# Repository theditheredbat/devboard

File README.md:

# DevBoard
I decided to follow along with HackClub's Devboard tutorial,  
made by Kai Pereira, to get more comfortable with designing PCBs.  
Here's what I ended up with:  

## PCB
Made in KiCAD  
Schematic:  

PCB:  

## BOM
1x [RP2040](https://jlcpcb.com/partdetail/RaspberryPi-RP2040/C2040) $0.92  
1x [PCB](https://cart.jlcpcb.com/quote?spm=Jlcpcb.Homepage.1006) from JLCPCB $2.10  
2x [33pF Capacitors](https://jlcpcb.com/partdetail/1914-0402CG330J500NT/C1562) $0.01  
11x [0.1uF Capacitors](https://jlcpcb.com/partdetail/1877-CL05B104KO5NNNC/C1525) $0.01  
2x [1uF Capacitors](https://jlcpcb.com/partdetail/15107-CL05A105KP5NNNC/C14445) $0.01  
2x [10uF Capacitors](https://jlcpcb.com/partdetail/2043-CL10A106MQ8NNNC/C1691) $0.01  
2x [27 Resistors](https://jlcpcb.com/partdetail/2358-RCMT08W270JT/C2006) $0.01  
2x [1K Resistors](https://jlcpcb.com/partdetail/12256-0402WGF1001TCE/C11702) $0.01  
2x [5.1K Resistors](https://jlcpcb.com/partdetail/26684-0402WGJ0512TCE/C25941) $0.01  
1x [10K Resistor](https://jlcpcb.com/partdetail/26274-0402WGJ0103TCE/C25531) $0.01  
1x [PinHeader1x03P2.54mm_Vertical](https://jlcpcb.com/partdetail/HanElectricity-2541WR03P/C5383096) $0.01  
2x [PinHeader1x20P2.54mm_Vertical](https://jlcpcb.com/partdetail/244951-2_54_1_20P/C247921) $0.23  
1x [4Pin 2x2.5mm Quartz Clock](https://jlcpcb.com/partdetail/YXC_CrystalOscillators-X322512MSB4SI/C9002) $0.06  
1x [USB-C Receptacle](https://jlcpcb.com/partdetail/Korean_HropartsElec-TYPE_C_31_M12/C165948) $0.17  
1x [TS-1088-AR02016 Push Button](https://jlcpcb.com/partdetail/XUNPU-TS_1088AR02016/C720477) $0.04  
1x [MCP1700x-330xxTT Fixed Voltage Regulator](https://jlcpcb.com/partdetail/JLCPCBAssembly-MCP1700/C9900006637) $0.39  
1x [W25Q16JVZPIQ TR Flash Mem Chip](https://jlcpcb.com/partdetail/WinbondElec-W25Q16JVZPIQ/C377853) $0.35  
Estimated Shipping: $2.40
Estimated Total: $6.92

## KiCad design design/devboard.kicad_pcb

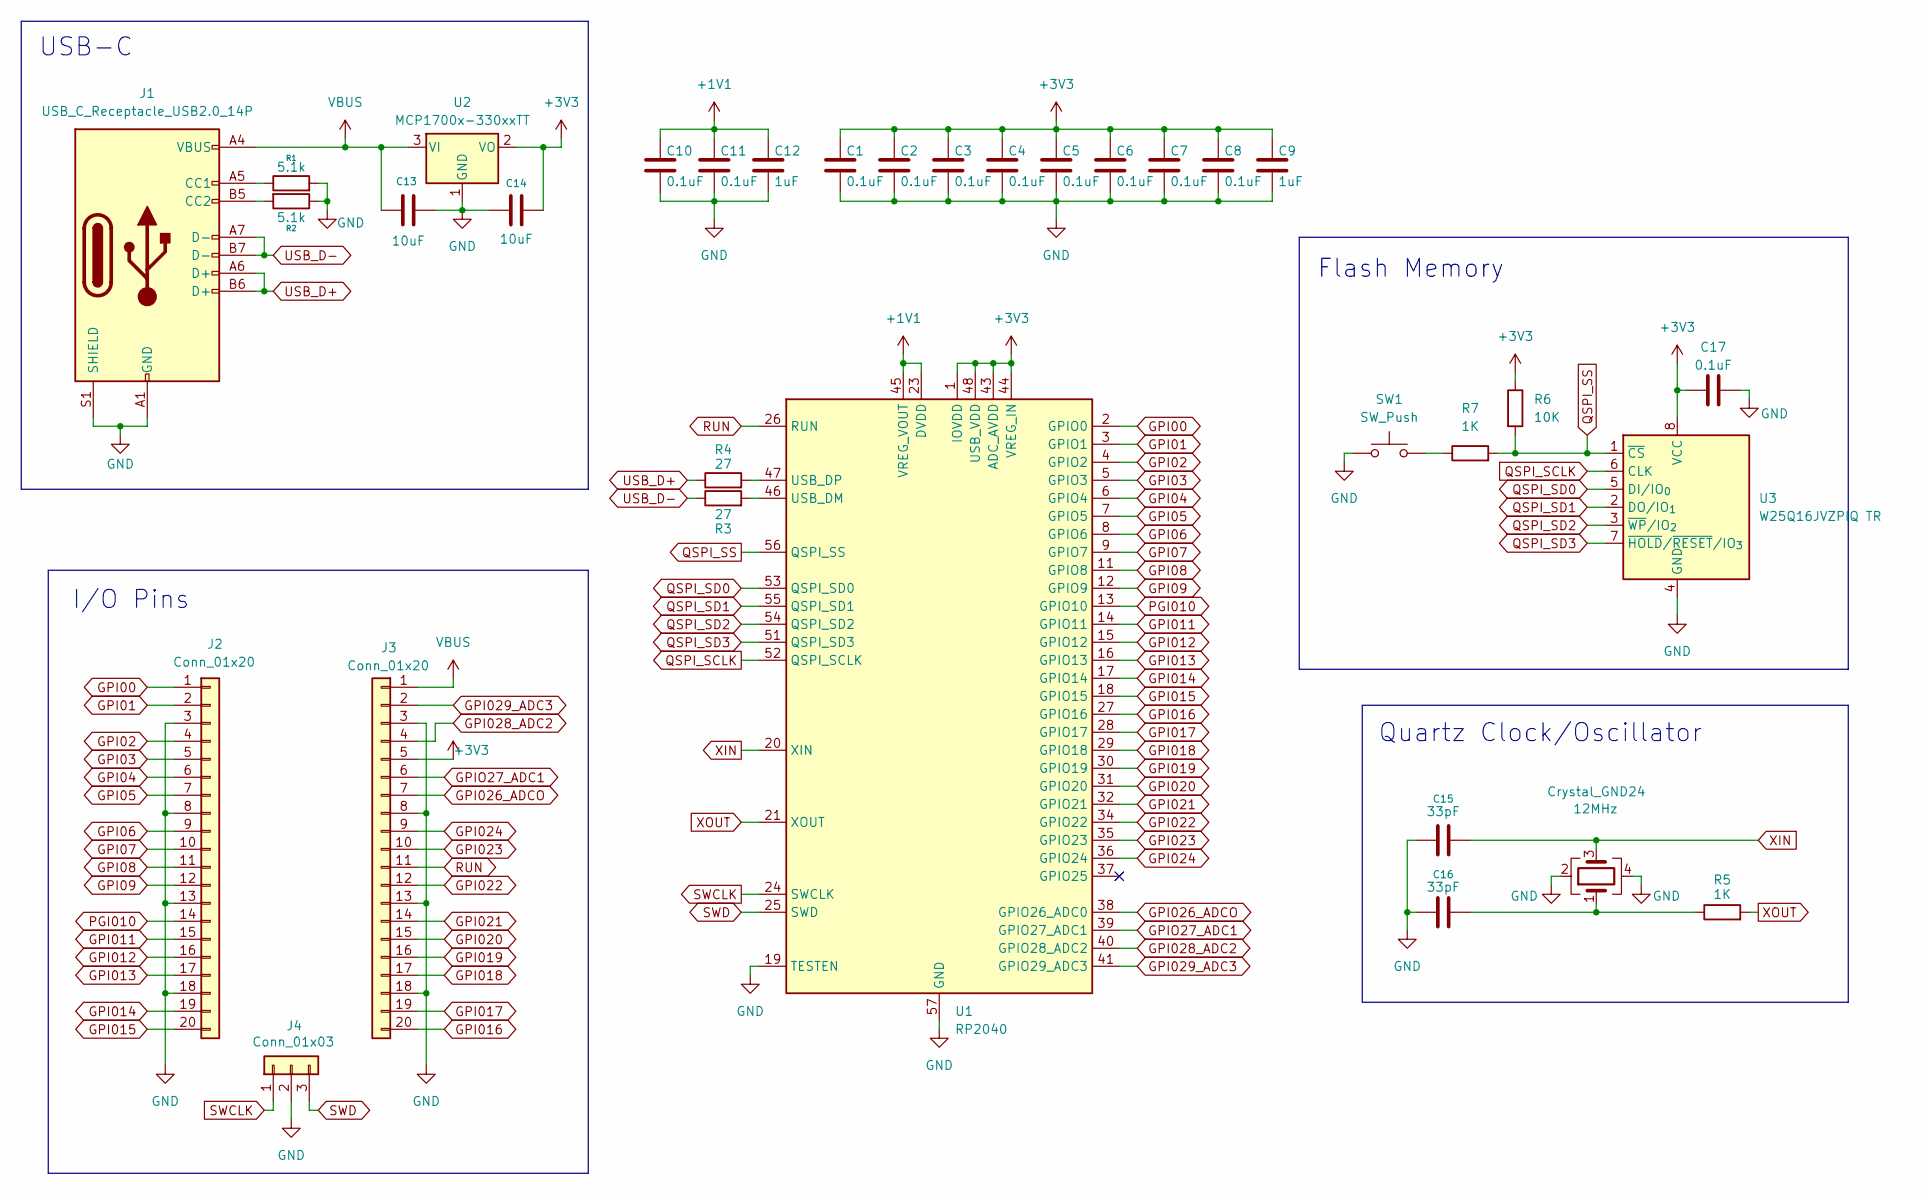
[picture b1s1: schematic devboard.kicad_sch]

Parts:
C1, C2, C3, C4, C5, C6, C7, C8, C10, C11, C17: 0.1uF; C_0402_1005Metric
C9, C12: 1uF; C_0402_1005Metric
C13, C14: 10uF; C_0603_1608Metric
C15, C16: 33pF; C_0402_1005Metric
Crystal_GND24: 12MHz; Crystal_SMD_3225-4Pin_3.2x2.5mm
J1: USB_C_Receptacle_USB2.0_14P; USB_C_Receptacle_HRO_TYPE-C-31-M-12
J2, J3: Conn_01x20; PinHeader_1x20_P2.54mm_Vertical
J4: Conn_01x03; PinHeader_1x03_P2.54mm_Vertical
R1, R2: 5.1k; R_0402_1005Metric
R3, R4: 27; R_0402_1005Metric
R5, R7: 1K; R_0402_1005Metric
R6: 10K; R_0402_1005Metric
SW1: SW_Push; SW_Push_SPST_NO_Alps_SKRK
U1: RP2040; QFN-56-1EP_7x7mm_P0.4mm_EP3.2x3.2mm
U2: MCP1700x-330xxTT; SOT-23
U3: W25Q16JVZPIQ TR; Winbond_USON-8-1EP_3x2mm_P0.5mm_EP0.2x1.6mm

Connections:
+1V1: C10.1, C11.1, C12.1, U1.23 (DVDD), U1.45 (VREG_VOUT), U1.50 (DVDD)
+3V3: C1.1, C2.1, C3.1, C4.1, C5.1, C6.1, C7.1, C8.1, C9.1, C14.2, C17.1, J3.5, R6.1, U1.1 (IOVDD), U1.10 (IOVDD), U1.22 (IOVDD), U1.33 (IOVDD), U1.42 (IOVDD), U1.43 (ADC_AVDD), U1.44 (VREG_IN), U1.48 (USB_VDD), U1.49 (IOVDD), U2.2 (VO), U3.8 (VCC)
GND: C1.2, C2.2, C3.2, C4.2, C5.2, C6.2, C7.2, C8.2, C9.2, C10.2, C11.2, C12.2, C13.2, C14.1, C15.1, C16.1, C17.2, Crystal_GND24.2, Crystal_GND24.4, J1.A1 (GND), J1.A12 (GND), J1.B1 (GND), J1.B12 (GND), J1.S1 (SHIELD), J2.3, J2.8, J2.13, J2.18, J3.3, J3.8, J3.13, J3.18, J4.2, R1.2, R2.1, SW1.1, U1.19 (TESTEN), U1.57 (GND), U2.1 (GND), U3.4 (GND); also elsewhere on the board
GPI00: J2.1, U1.2 (GPIO0)
GPI01: J2.2, U1.3 (GPIO1)
GPI02: J2.4, U1.4 (GPIO2)
GPI03: J2.5, U1.5 (GPIO3)
GPI04: J2.6, U1.6 (GPIO4)
GPI05: J2.7, U1.7 (GPIO5)
GPI06: J2.9, U1.8 (GPIO6)
GPI07: J2.10, U1.9 (GPIO7)
GPI08: J2.11, U1.11 (GPIO8)
GPI09: J2.12, U1.12 (GPIO9)
GPI011: J2.15, U1.14 (GPIO11)
GPI012: J2.16, U1.15 (GPIO12)
GPI013: J2.17, U1.16 (GPIO13)
GPI014: J2.19, U1.17 (GPIO14)
GPI015: J2.20, U1.18 (GPIO15)
GPI016: J3.20, U1.27 (GPIO16)
GPI017: J3.19, U1.28 (GPIO17)
GPI018: J3.17, U1.29 (GPIO18)
GPI019: J3.16, U1.30 (GPIO19)
GPI020: J3.15, U1.31 (GPIO20)
GPI021: J3.14, U1.32 (GPIO21)
GPI022: J3.12, U1.34 (GPIO22)
GPI023: J3.10, U1.35 (GPIO23)
GPI024: J3.9, U1.36 (GPIO24)
GPI026_ADCO: J3.7, U1.38 (GPIO26_ADC0)
GPI028_ADC2: J3.4, U1.40 (GPIO28_ADC2)
GPI029_ADC3: J3.2, U1.41 (GPIO29_ADC3)
GPIO27_ADC1: J3.6, U1.39 (GPIO27_ADC1)
unnamed 31: C16.2, Crystal_GND24.1, R5.1; also elsewhere on the board
unnamed: J1.A5 (CC1), R1.1
unnamed: J1.B5 (CC2), R2.2
unnamed: R7.1, SW1.2
unnamed: R3.2, U1.46 (USB_DM)
unnamed: R4.2, U1.47 (USB_DP)
PGI010: J2.14, U1.13 (GPIO10)
QSPI_SCLK: U1.52 (QSPI_SCLK), U3.6 (CLK)
QSPI_SD0: U1.53 (QSPI_SD0), U3.5 (DI/IO_{0})
QSPI_SD1: U1.55 (QSPI_SD1), U3.2 (DO/IO_{1})
QSPI_SD2: U1.54 (QSPI_SD2), U3.3 (~WP/IO_{2})
QSPI_SD3: U1.51 (QSPI_SD3), U3.7 (~HOLD/~RESET/IO_{3})
QSPI_SS: R6.2, R7.2, U1.56 (QSPI_SS), U3.1 (~CS)
RUN: J3.11, U1.26 (RUN)
SWCLK: J4.1, U1.24 (SWCLK)
SWD: J4.3, U1.25 (SWD)
USB_D+: J1.A6 (D+), J1.B6 (D+), R4.1
USB_D-: J1.A7 (D-), J1.B7 (D-), R3.1
VBUS: C13.1, J1.A4 (VBUS), J1.A9 (VBUS), J1.B4 (VBUS), J1.B9 (VBUS), J3.1, U2.3 (VI)
XIN: C15.2, Crystal_GND24.3, U1.20 (XIN); also elsewhere on the board
XOUT: R5.2, U1.21 (XOUT)

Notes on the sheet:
I/O Pins
Flash Memory
Quartz Clock/Oscillator
USB-C

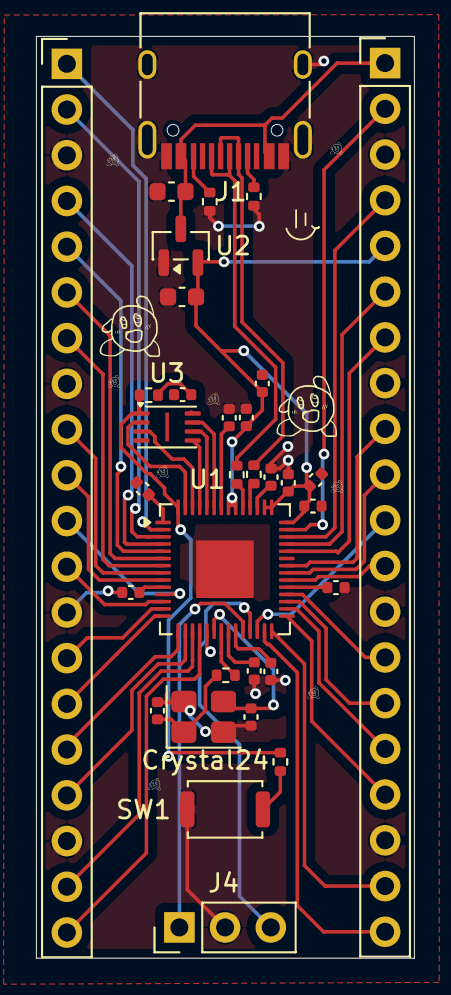
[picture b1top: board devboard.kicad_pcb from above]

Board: 2 copper layers, 21.0 x 51.2 mm, 41 parts (0 on the bottom side), 52 nets.

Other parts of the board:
Crystal24: 12MHz; Crystal_SMD_3225-4Pin_3.2x2.5mm
\n: LOGO
\n#2, \n#3, \n#4, \n#5, \n#6, \n#7, \n#8: LOGO

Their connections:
GND: Crystal24.2, Crystal24.4; also elsewhere on the board
unnamed 31: Crystal24.1; also elsewhere on the board
XIN: Crystal24.3; also elsewhere on the board

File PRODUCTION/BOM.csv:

Bill of Materials - Spreadsheet ver. (Everything from JLCPCB),,,,,,,,,,,
PCB Assembled Qty: 5,,Est. Total Price: 11.562 (from Devboard tutorial),,,,,,,,,
Designator,Comment,Footprint,,,JLCPCB Part,Part #,Manufacturer,,Qty,Price,Link to JLCPCB page
R6,10K,R_0402_1005Metric,,,,0402WGJ0103TCE,UNI-ROYAL(Uniroyal Elec),,1,0.01,https://jlcpcb.com/partdetail/26274-0402WGJ0103TCE/C25531
"R5, R7",1K,R_0402_1005Metric,,,,0402WGF1001TCE,UNI-ROYAL(Uniroyal Elec),,2,0.01,https://jlcpcb.com/partdetail/12256-0402WGF1001TCE/C11702
"R3, R4",27,R_0402_1005Metric,,,,RC-MT08W270JT,FH (Guangdong Fenghua Advanced Tech) ,,2,0.01,https://jlcpcb.com/partdetail/2358-RCMT08W270JT/C2006
"R1, R2",5.1K,R_0402_1005Metric,,,,0402WGJ0512TCE,UNI-ROYAL(Uniroyal Elec),,2,0.01,https://jlcpcb.com/partdetail/26684-0402WGJ0512TCE/C25941
"C1, C2, C3, C4, C5, C6, C7, C8, C10, C11, C17",0.1uF,C_0402_1005Metric,,,,CL05B104KO5NNNC,Samsung Electro-Mechanics,,11,0.01,https://jlcpcb.com/partdetail/1877-CL05B104KO5NNNC/C1525
"C9, C12",1uF,C_0402_1005Metric,,,,CL05A105KP5NNNC,Samsung Electro-Mechanics,,2,0.01,https://jlcpcb.com/partdetail/15107-CL05A105KP5NNNC/C14445
"C15, C16",33pF,C_0402_1005Metric,,,,0402CG330J500NT,FH (Guangdong Fenghua Advanced Tech) ,,2,0.01,https://jlcpcb.com/partdetail/1914-0402CG330J500NT/C1562
"C13, C14",10uF,C_0603_1608Metric,,,,CL10A106MQ8NNNC,Samsung Electro-Mechanics,,2,0.01,https://jlcpcb.com/partdetail/2043-CL10A106MQ8NNNC/C1691
Crystal_GND24,12MHz,Crystal_SMD_3225-4Pin_3.2x2.5mm,,,,X322512MSB4SI,YXC Crystal Oscillators,,1,0.06,https://jlcpcb.com/partdetail/YXC_CrystalOscillators-X322512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
J1,USB_C_Receptacle_USB2.0_14P,USB_C_Receptacle_HRO_TYPE-C-31-M-12,,,,TYPE-C-31-M-12,Korean Hroparts Elec,,1,0.17,https://jlcpcb.com/partdetail/Korean_HropartsElec-TYPE_C_31_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
J2. J3,Conn_01x20,PinHeader_1x20_P2.54mm_Vertical,,,,2.54-1*20P反弯针,BOOMELE(Boom Precision Elec),,2,0.23,https://jlcpcb.com/partdetail/244951-2_54_1_20P/C247921
J4,Conn_01x03,PinHeader_1x03_P2.54mm_Vertical,,,,2541WR-03P,HanElectricity,,1,0.01,https://jlcpcb.com/partdetail/HanElectricity-2541WR03P/C5383096
SW1,SW_Push,SW_Push_SPST_NO_Alps_SKRK,,,,TS-1088-AR02016,XUNPU,,1,0.04,https://jlcpcb.com/partdetail/XUNPU-TS_1088AR02016/C720477
U1,RP2040,QFN-56-1EP_7x7mm_P0.4mm_EP3.2x3.2mm,,,,RP2040,Raspberry Pi,,1,0.92,https://jlcpcb.com/partdetail/RaspberryPi-RP2040/C2040
U2,MCP1700x-330xxTT,SOT-23,,,,MCP1700T-3302E/TT,Microchip Tech,,1,0.39,https://jlcpcb.com/partdetail/JLCPCBAssembly-MCP1700/C9900006637
U3,W25Q16JVZPIQ TR,Winbond_USON-8-1EP_3x2mm_P0.5mm_EP0.2x1.6mm,,,,W25Q16JVZPIQ,Winbond Elec,,1,0.35,https://jlcpcb.com/partdetail/WinbondElec-W25Q16JVZPIQ/C377853

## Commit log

2025-12-05 Fixed Images
2025-12-05 Fixed README Formatting
2025-12-05 Fixed README Linebreaks
2025-12-05 Fixed README Filepath
2025-12-05 Added BOM to README
2025-12-05 Added KiCAD generated BOM .csv file to PRODUCTION folder
2025-12-05 Renamed BOM
2025-12-05 Pricing in README
2025-12-05 Links in README
2025-12-06 Added links to spreadsheet
2025-12-06 Switched spreadsheat from .xlsx to .csv
